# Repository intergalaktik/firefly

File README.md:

# Firefly

Board is designed to run custom made panels designed by Novena.

Designed to drive LED strip WS28121/WS28121

Depending on components and jumpers board can be sender or receiver. 

RJ45 connector is used as it is cheap.

UTP Cables are cheap and easily available.

Sender board is connected over USB to computer.

Currently sender board is just use as USB > RS485 pass

On receiver board switches are used to set panel ID

On computer software we can assign each LED to one or more groups and change group color with just one message.

Currently this board is using custom designed RS485 protocol.

Simple example of using LED group

https://www.youtube.com/watch?v=NDzNr1LaLNI

Example with more features implemented

https://youtu.be/98tDE7uqz9s

Testing blender render 

https://www.youtube.com/watch?v=SnCAtjjVjGQ

Parts of schematics are from:

https://github.com/TimGremalm/LightBoxNano

PCBart blender style

https://github.com/pcbarts/stylized-blender-setup

40 pcs. batch for museum installation

DMX test

https://www.youtube.com/watch?v=Ih8ujr5BlC8

https://www.youtube.com/watch?v=qBxfGmqJY24

https://www.youtube.com/watch?v=aGFyOSpUzw4

https://www.youtube.com/watch?v=s4EHGpA8z-Q&t=11s

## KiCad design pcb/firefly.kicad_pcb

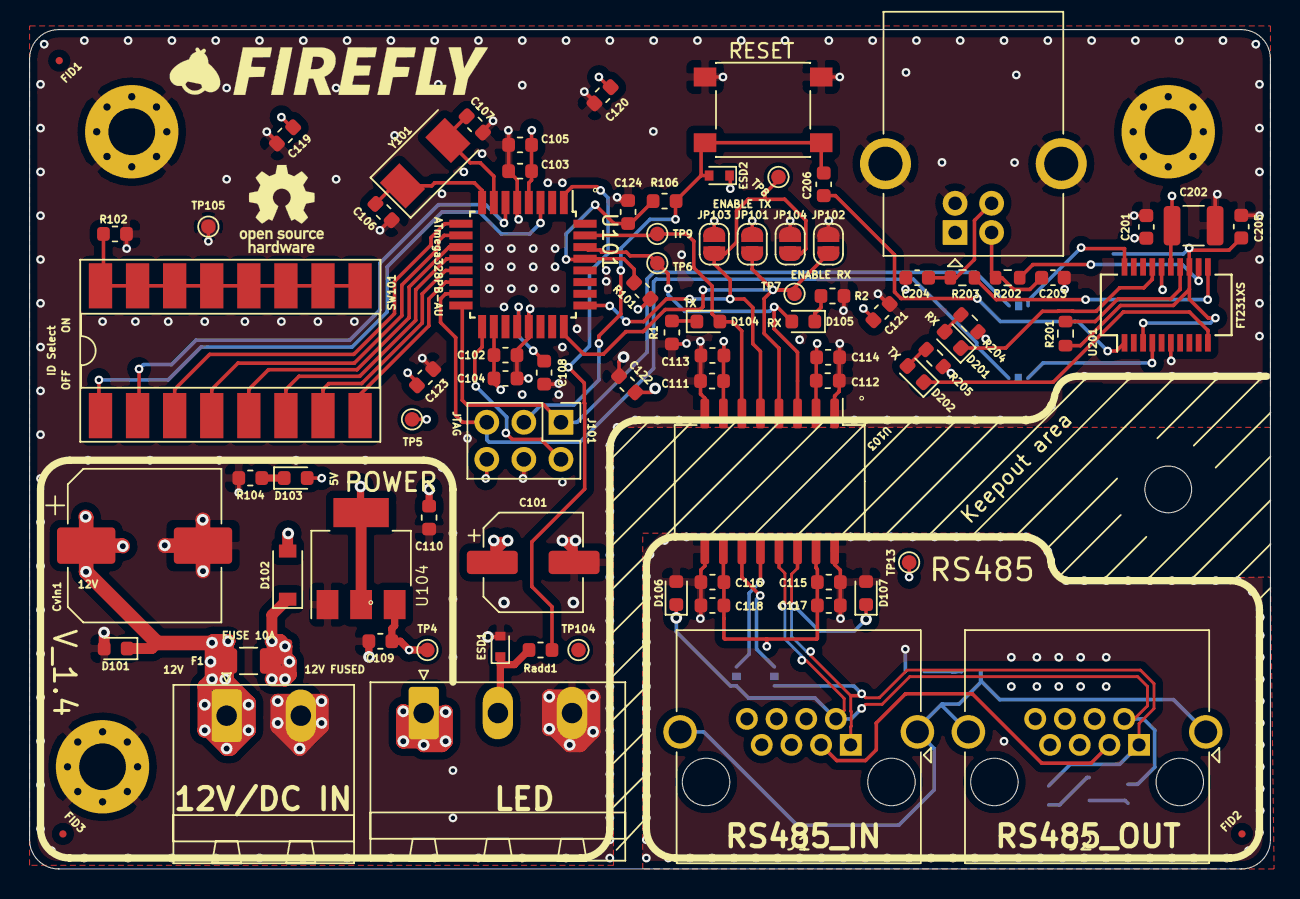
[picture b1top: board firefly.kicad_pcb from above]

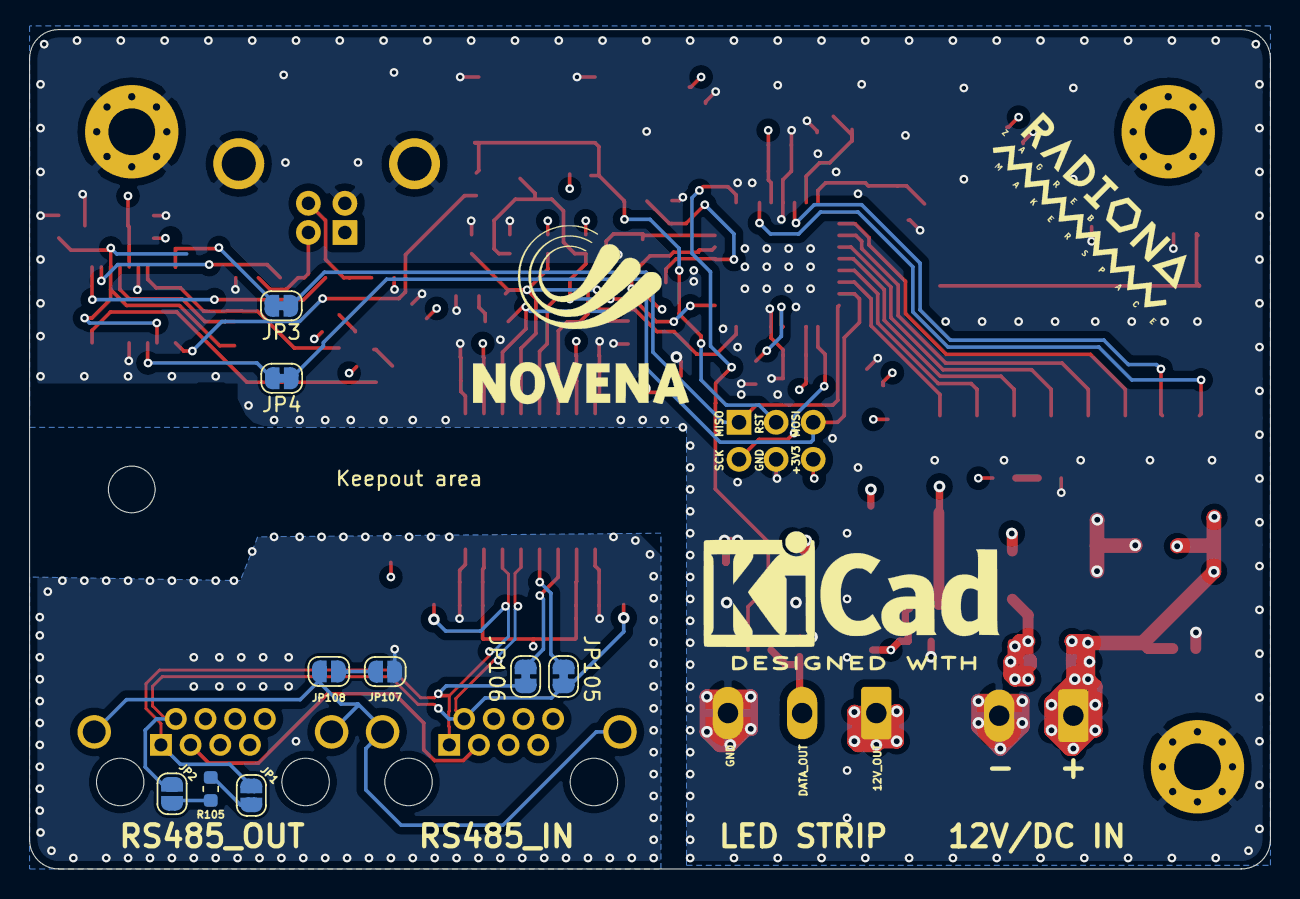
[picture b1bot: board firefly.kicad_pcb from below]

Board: 4 copper layers, 85.0 x 57.5 mm, 97 parts (9 on the bottom side), 54 nets.

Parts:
C101: 100uF/16V; CP_Elec_6.3x5.3
C102, C103, C108, C113, C114, C117, C118, C119, C120, C121, C122, C123, C124, C206: 100n; C_0603_1608Metric
C104, C105, C111, C112, C115, C116: 10n; C_0603_1608Metric
C106, C107: 22pF; C_0603_1608Metric
C109, C110: 1uF; C_0603_1608Metric
C201, C205: 100nF; C_0603_1608Metric
C202: 4.7µF; C_1210_3225Metric
C203, C204: 47pF; C_0603_1608Metric
Cvin1: 100µF 50V 27mΩ; CP_Elec_10x10
D101, D106, D107: 82306120029; D_0603_1608Metric
D102: D_Schottky_Small; D_SOD-123
D103: LED_3V; LED_0603_1608Metric
D104, D105: LED_5V; LED_0603_1608Metric
D201: RX; LED_0603_1608Metric
D202: TX; LED_0603_1608Metric
ESD1, ESD2: PESD5V0X1UAB; D_SOD-523
F1: Fuse DNP; Fuse_1206_3216Metric_Pad1.42x1.75mm_HandSolder
FID1: FID_ATM; Fiducial_0.5mm_Mask1mm
FID2: FID_GUL; Fiducial_0.5mm_Mask1mm
FID3: FID_TLV; Fiducial_0.5mm_Mask1mm
H1, H2, H4: MountingHole; MountingHole_3.2mm_M3_Pad_Via
H3: MountingHole; MountingHole_3.2mm_M3
J1, J2: RJ45_Shielded; RJ45_Amphenol_RJHSE5380
J3: USB_B; USB_B_OST_USB-B1HSxx_Horizontal
J101: Conn_02x03_Counter_Clockwise; PinHeader_2x03_P2.54mm_Vertical
JP1: ET1; SolderJumper-2_P1.3mm_Open_RoundedPad1.0x1.5mm
JP2: ET2; SolderJumper-2_P1.3mm_Open_RoundedPad1.0x1.5mm
JP3: JP_FTDI_TX; SolderJumper-2_P1.3mm_Bridged_RoundedPad1.0x1.5mm
JP4: JP_FTDI_RX; SolderJumper-2_P1.3mm_Bridged_RoundedPad1.0x1.5mm
JP101: Receiver_Disable1; SolderJumper-2_P1.3mm_Open_RoundedPad1.0x1.5mm
JP102: Receiver_Enable1; SolderJumper-2_P1.3mm_Open_RoundedPad1.0x1.5mm
JP103: Driver_Enable1; SolderJumper-2_P1.3mm_Open_RoundedPad1.0x1.5mm
JP104: Driver_Disable1; SolderJumper-2_P1.3mm_Open_RoundedPad1.0x1.5mm
JP105, JP106: SolderJumper_2_Open; SolderJumper-2_P1.3mm_Bridged_RoundedPad1.0x1.5mm
JP107, JP108: SolderJumper_2_Open; SolderJumper-2_P1.3mm_Open_RoundedPad1.0x1.5mm
Jadd1: MSTBA3; PhoenixContact_MSTBA_2,5_3-G-5,08_1x03_P5.08mm_Horizontal
Jc1: MSTBA2; PhoenixContact_MSTBA_2,5_2-G-5,08_1x02_P5.08mm_Horizontal
R1, R2, R104, R106: 300; R_0603_1608Metric
R101: 4K7; R_0603_1608Metric
R102: 1K; R_0603_1608Metric
R105: 120R; R_0603_1608Metric
R201: 100K; R_0603_1608Metric
R202, R203: 27R; R_0603_1608Metric
R204, R205: 270R; R_0603_1608Metric
Radd1: 1k; R_0603_1608Metric
SW101: SW_DIP_x08; DIP-16_W8.89mm_SMDSocket_LongPads
SW102: RESET; SW_SPST_PTS645
TP4: TP_Vin; TestPoint_Pad_D1.0mm
TP5: TP_3V3; TestPoint_Pad_D1.0mm
TP6: DMX_RX; TestPoint_Pad_D1.0mm
TP7: DMX_RE; TestPoint_Pad_D1.0mm
TP8: DMX_DE; TestPoint_Pad_D1.0mm
TP9: DMX_TX; TestPoint_Pad_D1.0mm
TP13: DMX_3V3; TestPoint_Pad_D1.0mm
TP104: TP_A; TestPoint_Pad_D1.0mm
TP105: TP_GND1; TestPoint_Pad_D1.0mm
U101: ATmega328PB-AU; TQFP-32_7x7mm_P0.8mm
U103: ADM2687E; SOIC-16W_7.5x12.8mm_P1.27mm
U104: AMS1117; SOT-223-3_TabPin2
U201: FT231XS; SSOP-20_3.9x8.7mm_P0.635mm
Y101: 16MHz; Crystal_SMD_0603-2Pin_6.0x3.5mm

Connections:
+3V3: C101.1, C102.1, C103.1, C104.1, C105.1, C110.1, C111.1, C112.2, C113.2, C114.1, C119.1, C120.1, C121.1, C122.1, C123.1, C201.1, C202.1, D102.2, D103.2, ESD2.1, J3.1, J101.6, JP101.1, JP103.1, R101.2, R204.1, R205.1, TP5.1, U101.4, U101.18, U103.2, U103.7, U104.2, U201.15
/Addressable: Radd1.2, U101.1
/DMX_Enable_Receive: JP101.2, JP102.1, TP7.1, U101.24, U103.4
/DMX_Enable_Send: JP103.2, JP104.1, TP8.1, U101.25, U103.5
/DMX_Receive: D105.2, TP6.1, U101.30, U103.3
/DMX_Send: D104.2, TP9.1, U101.31, U103.6
/MISO: J101.1, JP3.1, U101.16
/MOSI: J101.5, JP4.1, U101.15
/RS485_transciever/DMX+: D107.1, J1.1, J2.1, JP1.1, JP106.2, U103.14
/RS485_transciever/DMX-: D106.1, J1.2, J2.2, JP2.2, JP105.2, U103.13
/RS485_transciever/DMXTransmitterY: JP106.1, U103.11
/RS485_transciever/DMXTransmitterZ: JP105.1, U103.12
/RS485_transciever/DMXchassignd: J1.SH, J2.SH, JP108.2
/RS485_transciever/DMXgnd: JP107.2, JP108.1
/RS485_transciever/DXMgnd: J1.3, J2.3
/RST: C206.2, ESD2.2, J101.3, R106.2, SW102.2
/SCK: J101.2, U101.17
/SW_1: SW101.1, U101.3
/SW_2: SW101.2, U101.6
/SW_3: SW101.3, U101.9
/SW_4: SW101.4, U101.10
/SW_5: SW101.5, U101.11
/SW_6: SW101.6, U101.12
/SW_7: SW101.7, U101.13
/SW_8: SW101.8, U101.14
/USB-serial/FTDI_RXD: JP4.2, U201.4
/USB-serial/FTDI_TXD: JP3.2, U201.20
/Vin: Cvin1.1, D101.1, F1.2, Jc1.1
DMX_3V: C115.1, C116.2, C117.1, C118.2, TP13.1, U103.10, U103.15
GND1: C101.2, C102.2, C103.2, C104.2, C105.2, C106.2, C107.2, C108.2, C109.2, C110.2, C111.2, C112.1, C113.1, C114.2, C119.2, C120.2, C121.2, C122.2, C123.2, C124.2, C201.2, C202.2, C203.2, C204.2, C205.1, Cvin1.2, D101.2, ESD1.2, H1.1, H2.1, H4.1, J3.4, J3.5, J101.4, JP102.2, JP104.2, Jadd1.3, Jc1.2, R1.1, R2.1, R102.1, R104.1, SW102.1, TP105.1, U101.5, U101.21, U103.1, U103.8, U104.1, U201.6, U201.16
GND2: C115.2, C116.1, C117.2, C118.1, D106.2, D107.2, JP107.1, U103.9, U103.16
unnamed: C106.1, U101.8, Y101.1
unnamed: C107.1, U101.7, Y101.2
unnamed: C108.1, U101.20
unnamed: C124.1, R101.1, R106.1, U101.29
unnamed: C203.1, J3.2, R202.2
unnamed: C204.1, J3.3, R203.2
unnamed: C205.2, R201.1, U201.3, U201.13
unnamed: C206.1, U201.1
unnamed: D103.1, R104.2
unnamed: D104.1, R1.2
unnamed: D105.1, R2.2
unnamed: D201.1, U201.17
unnamed: D201.2, R204.2
unnamed: D202.1, U201.10
unnamed: D202.2, R205.2
unnamed: ESD1.1, Jadd1.2, Radd1.1
unnamed: JP1.2, R105.1
unnamed: JP2.1, R105.2
unnamed: R102.2, SW101.9, SW101.10, SW101.11, SW101.12, SW101.13, SW101.14, SW101.15, SW101.16
unnamed: R201.2, U201.14
unnamed: R202.1, U201.12
unnamed: R203.1, U201.11
Vin_fused: C109.1, D102.1, F1.1, Jadd1.1, TP4.1, U104.3

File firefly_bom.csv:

References,Qty,Description,Manufacturer,MPN,Manufacturer,MPN,Manufacturer,MPN,Digikey,Mouser,RS,Newark,Farnell
Cvin1,1,100uF 50V 27m?  CP_Elec_10x10,Cornell Dubilier,AFK107M63G24T-F,,,,,338-2146-6-ND,5985AFK63V100F,,,2131903
C101,1,100uF/16V CP_Elec_6.3x5.3,Panasonic,16SVPT100M,,,,,10-16SVPT100MDKR-ND,66716SVPT100M,2018078,,3266925
"C102, C103, C108, C113, C114, C117, C118, C119, C120, C121, C122, C123, C124, C201, C205, C206",16,100n  C_0603_1608Metric,Würth Elektronik,885012206046,,,,,732-7965-6-ND,710885012206046,8392811,,2495170
"C104, C105, C111, C112, C115, C116",6,10n C_0603_1608Metric,Würth Elektronik,885012206040,,,,,732-7959-6-ND,710885012206040,8392798,,2534021
"C106, C107",2,22pF  C_0603_1608Metric,Würth Elektronik,885012006019,,,,,732-7762-6-ND,710885012006019,1813967,,2533830
"C109, C110",2,1uF C_0603_1608Metric,KEMET,C0603C105K8PAC,,,,,,80C0603C105K8PAC,,,
"C203, C204",2,47pF  C_0603_1608Metric,Würth Elektronik,885012006021,,,,,732-7764-1-ND,710885012006021,1813913,,2812096
C202,1,4.7uF C_1210_3225Metric,Würth Elektronik,885012107013,,,,,732-7623-1-ND,710885012107013,1813918,,2533952
"R1, R2, R104, R106",4,300 R_0603_1608Metric,Yageo,RC0603JR-07300RL,,,,,311-300GRCT-ND,603RC0603JR07300RL,,,1799420
"R102, Radd1",2,1K  R_0603_1608Metric,Yageo,RC0603JR-071KL,,,,,311-1.0KGRCT-ND,603RC0603JR071KL,,,1799376
"R202, R203",2,27R R_0603_1608Metric,Yageo,RC0603FR-0727RL,,,,,311-27.0HRCT-ND,603RC0603FR0727RL,,,2693669
"R204, R205",2,270R  R_0603_1608Metric,Yageo,AC0603FR-07270RL,,,,,13-AC0603FR-07270RLDKR-ND,603AC0603FR07270RL,,,
R101,1,4K7 R_0603_1608Metric,rohm,SFR03EZPF4701,,,,,511-1822-1-ND,755SFR03EZPF4701,,,2887235
R105,1,120R  R_0603_1608Metric,Yageo,RC0603FR-07130RL,,,,,311-130HRDKR-ND,603RC0603FR07130RL,,,3495733
R201,1,100K  R_0603_1608Metric,Vishay,RCA0603100KJNEC,,,,,541-3895-6-ND,71RCA0603100KJNEC,1885639,,3546686
D102,1,D_Schottky_Small  D_SOD-123,MCC,MBR0530-TP,,,,,MBR0530TPMSCT-ND,833MBR0530TP,,,1924376
"D104, D105",2,LED_5V  LED_0603_1608Metric,Lite-On,LTST-C190GKT,,,,,160-1183-1-ND,859LTSTC190GKT,6920975,,
D103,1,LED_3V  LED_0603_1608Metric,Lite-On,LTST-C190EKT,,,,,160-1182-1-ND,859LTSTC190EKT,6920972,,
D201,1,RX  LED_0603_1608Metric,Lite-On,LTST-C190EKT,,,,,160-1182-1-ND,859LTSTC190EKT,6920972,,
D202,1,TX  LED_0603_1608Metric,Lite-On,LTST-C190GKT,,,,,160-1183-1-ND,859LTSTC190GKT,6920975,,
U103,1,ADM2687E  SOIC-16W_7.5x12.8mm_P1.27mm,Analog Devices,ADM2687EBRIZ,,,,,ADM2687EBRIZ-ND,584ADM2687EBRIZ,7968972P,,2008784
U104,1,AMS1117 SOT-223-3_TabPin2,STMicroelectronics,LD1117S50TR,,,,,497-6447-1-ND,511LD1117S50,6869379,,1467781
Y101,1,16MHz Crystal_SMD_0603-2Pin_6.0x3.5mm,ECS International,ECS-160-18-23G-JGN-TR,ECS International,ECS-160-18-23B-JTM-TR,,,XC3086DKR-ND,52016.01823GJGNT,,,
F1,1,Fuse DNP  Fuse_1206_3216Metric_Pad1.42x1.75mm_HandSolder,Littelfuse,0458010.DR,,,,,F2941DKR-ND,5760458010.DR,1740289,,1692861
SW101,1,SW_DIP_x08  DIP-16_W8.89mm_SMDSocket_LongPads,CTS Components,219-8MST,,,,,CT2198MST-ND,7742198MST,1774234,,
SW102,1,RESET SW_SPST_PTS645,C&K Components,PTS645SL50SMTR92LFS,,,,,CKN9088DKR-ND,611PTS645SL50SMTR92,1359177,,2435163RL
"ESD1, ESD2",2,PESD5V0X1UAB  D_SOD-323_HandSoldering,Nexperia,"PESD5V0X1UAB,115",,,,,1727-1324-1-ND,771PESD5V0X1UAB115,7918933P,,2069370
Jc1,1,"MSTBA2  PhoenixContact_MSTBA_2,5_2-G-5,08_1x02_P5.08mm_Horizontal",Phoenix Contact,1748167,Phoenix Contact,1748167,Phoenix Contact,1755736,277-1150-ND,6511755736,1896199,,3705262
Jadd1,1,"MSTBA3  PhoenixContact_MSTBA_2,5_3-G-5,08_1x03_P5.08mm_Horizontal",Phoenix Contact,1748183,,,,,277-8657-ND,6511748183,,,
"J1, J2",2,RJ45_Shielded RJ45_Amphenol_RJHSE5380,Amphenol,RJHSE-5380,,,,,RJHSE-5380-ND,523RJHSE5380,,,1849916
U201,1,FT231XS SSOP-20_3.9x8.7mm_P0.635mm,FTDI,FT231XS-U,,,,,768-1156-5-ND,895FT231XSU,8888722,,
J3,1,USB_B USB_B_TE_5787834_Vertical,TE Connectivity,5787834-1,,,,,5787834-1-ND,57157878341,5298224,,1076666
J101,1,Conn_02x03_Counter_Clockwise  PinHeader_2x03_P2.54mm_Vertical,,,,,,,,,,,
CONN1_EXT,1,2P 5.08mm PLUG,TE Connectivity,282807-2,,,,,A106364-ND,5712828072,7100422,,2059789
CONN2_EXT,1,3P 5.08mm PLUG,TE Connectivity,282807-3,,,,,A106365-ND,5712828073,7100429,,3133861

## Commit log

2021-02-12 Initial FireFly upload
2021-02-16 Adding 3D model
2021-03-08 fixing broken symbols
2021-03-08 Adding logos, fixing text
2021-03-08 Adding logos
2021-03-08 Before production export changes
2021-03-08 Adding v_1.3 schematics
2021-03-08 Adding interactive BOM
2021-03-08 Adding production files
2021-03-08 Adding files needed for kitspace
2021-03-08 Adding gerbers
2021-03-24 Change oscilator and 2 pin connector
2021-04-08 Adding protection diodes
2021-04-09 Changing USB connector - rerouting
2021-04-10 Adding two connectors with 4 analog inputs
2021-04-20 Adding pictures - README update
2022-10-19 Adding v1.5
2025-04-11 uređena schema
2025-04-11 unesene stavke koje su falile
2025-04-15 dodan pdf
